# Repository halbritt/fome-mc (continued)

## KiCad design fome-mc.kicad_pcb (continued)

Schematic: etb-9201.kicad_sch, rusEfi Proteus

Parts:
C201, C202: 10n; C_0603_1608Metric; LCSC C344025
C1201: 2.2u; C_1206_3216Metric; LCSC C90787
R210: 10k; R_0402_1005Metric; LCSC C25744
U201: TLE9201SG; Infineon_PG-DSO-12-9; LCSC C2653438

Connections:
+3V3: R210.2, U201.2 (VSO); also elsewhere on the board
/12V_MR: C1201.2, U201.4 (VS); also elsewhere on the board
/ETB1_DIR: U201.1 (DIR); also elsewhere on the board
/ETB1_DIS: R210.1, U201.11 (DIS); also elsewhere on the board
/ETB1_OUT+: C201.2, U201.5 (OUT1); also elsewhere on the board
/ETB1_OUT-: C202.1, U201.7 (OUT2); also elsewhere on the board
/ETB1_PWM: U201.12 (PWM); also elsewhere on the board

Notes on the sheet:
IFX9201 also acceptable

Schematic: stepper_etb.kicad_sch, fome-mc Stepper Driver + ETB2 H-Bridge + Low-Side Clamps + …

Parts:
C203: 10n; C_0603_1608Metric; LCSC C344025
C204, C205: 100n; C_0603_1608Metric; LCSC C161115
C206: 470n; C_0603_1608Metric; LCSC C1623
D201, D202, D203, D204: B340A-13-F; D_SMA; LCSC C85098; not fitted
D205, D206, D207, D208, D209: B340A-13-F; D_SMA; LCSC C85098
D210: BZT52C6V8; D_SOD-123; LCSC C173404
D211: B5819W; D_SOD-123; LCSC C8598
R209, R218: 12k; R_0402_1005Metric; LCSC C25752
R211: 1M; R_0603_1608Metric; LCSC C22935
R212: 2.2k; R_0603_1608Metric; LCSC C4190
R213, R214: 200m; R_1206_3216Metric; LCSC C25335
R215: 33k; R_0402_1005Metric; LCSC C25779
R216, R217: 10k; R_0402_1005Metric; LCSC C25744
U202: DRV8825PWPR; HTSSOP-28-1EP_4.4x9.7mm_P0.65mm_EP2.85x5.4mm; LCSC C81582
U203: TLE9201SG; Infineon_PG-DSO-12-9; LCSC C2653438

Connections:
+3V3: D211.1 (K), R215.1, U202.16 (nRESET), U202.17 (nSLEEP), U203.2 (VSO); also elsewhere on the board
/12V_MR: C204.2, C205.1, D201.1 (K), D202.1 (K), D203.1 (K), D204.1 (K), D205.1 (K), D206.1 (K), D207.1 (K), D208.1 (K), D209.1 (K), R211.2, R212.1, U202.4 (VMA), U202.11 (VMB), U203.4 (VS); also elsewhere on the board
/BOOT0_NET: R209.2; also elsewhere on the board
/ETB2_DIR: U203.1 (DIR); also elsewhere on the board
/ETB2_DIS: U203.11 (DIS); also elsewhere on the board
/ETB2_OUT+: U203.5 (OUT1); also elsewhere on the board
/ETB2_OUT-: U203.7 (OUT2); also elsewhere on the board
/ETB2_PWM: U203.12 (PWM); also elsewhere on the board
/LS1: D201.2 (A); also elsewhere on the board
/LS2: D202.2 (A); also elsewhere on the board
/LS3: D203.2 (A); also elsewhere on the board
/LS4: D204.2 (A); also elsewhere on the board
/LS5: D205.2 (A); also elsewhere on the board
/LS6: D206.2 (A); also elsewhere on the board
/LS7: D207.2 (A); also elsewhere on the board
/LS8: D208.2 (A), R212.2; also elsewhere on the board
/LS9: U202.22 (STEP); also elsewhere on the board
/LS12: U202.20 (DIR); also elsewhere on the board
/MAIN_RLY: D209.2 (A); also elsewhere on the board
/PB8_STEP_EN: U202.21 (nENBL); also elsewhere on the board
/RC2: D211.2 (A), R217.2, R218.1; also elsewhere on the board
/STEP_1A: U202.5 (AOUT1); also elsewhere on the board
/STEP_1B: U202.7 (AOUT2); also elsewhere on the board
/STEP_2A: U202.10 (BOUT1); also elsewhere on the board
/STEP_2B: U202.8 (BOUT2); also elsewhere on the board
/USB_VBUS_BOOT0: D210.1 (K), R217.1; also elsewhere on the board
unnamed: D210.2 (A), R209.1
unnamed: R215.2, R216.1, U202.12 (AVREF), U202.13 (BVREF)
unnamed: C203.1, U202.1 (CP1)
unnamed: C203.2, U202.2 (CP2)
unnamed: R213.1, U202.6 (ISENA)
unnamed: R214.1, U202.9 (ISENB)
unnamed: C206.1, U202.15 (V3P3OUT)
unnamed: C204.1, R211.1, U202.3 (VCP)

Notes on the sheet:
D201..D204: DNP on INJ1..4 (/LS1../LS4) so U1001/U1002 VNLD5090TR-E use internal 42V active clamp for fast injector turn-off. D205..D209: Populated on LS5..LS8 & MAIN_RLY inductive relay/solenoid channels.

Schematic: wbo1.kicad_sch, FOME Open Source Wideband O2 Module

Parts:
C301, C304, C306, C307, C317: 1u; C_0402_1005Metric; LCSC C52923
C302, C305, C308, C309, C311, C312, C313, C314, C316: 100n; C_0402_1005Metric; LCSC C1525
C303: 33n; C_0402_1005Metric; LCSC C415530
C310: 4.7u; C_0603_1608Metric; LCSC C19666
D301, D304: RED; LED_0603_1608Metric; LCSC C2286
D302: GREEN; LED_0603_1608Metric; LCSC C12624
D303: BLUE; LED_0603_1608Metric; LCSC C2288
Q301: VND14NV04; TO-252-2; LCSC C2649436
R301, R302, R313, R318, R325, R326, R327, R330: 1k; R_0402_1005Metric; LCSC C11702
R303, R304, R311, R312, R321, R329, R333, R334: 10k; R_0402_1005Metric; LCSC C25744
R305, R307: 27k; R_0402_1005Metric; LCSC C25771
R306: 22k; R_0402_1005Metric; LCSC C25768
R308: 47; R_0402_1005Metric; LCSC C25118
R309: 10; R_0402_1005Metric; LCSC C25077
R310: 61.9; R_0603_1608Metric; LCSC C2087389
R314: 62k; R_0603_1608Metric; LCSC C23221
R315, R317, R320: 100k; R_0402_1005Metric; LCSC C25741
R316: 6.8k; R_0402_1005Metric; LCSC C25917
R319: 47k; R_0402_1005Metric; LCSC C25792
R324: 3.3k; R_0402_1005Metric; LCSC C25890
R331, R332: 68k; R_0402_1005Metric; LCSC C36871
U301: MCP6004; TSSOP-14_4.4x5mm_P0.65mm; LCSC C50282
U302: STM32F042K6Tx; LQFP-32_7x7mm_P0.8mm; LCSC C69216
U303: REF3033; SOT-23; LCSC C36658
U305: AD8628; TSOT-23-5; LCSC C29309
U307: TJA1051T-3; SOIC-8_3.9x4.9mm_P1.27mm; LCSC C38695
U309: XC6206P332MR; SOT-23; LCSC C5446

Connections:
+3V3_WBO1: C305.1, C310.1, C312.1, C313.1, C314.1, R314.1, R318.2, U301.4 (V+), U302.1 (VDD), U302.17 (VDDIO2), U305.5 (V+), U307.5 (VIO), U309.2 (VO)
+5V: C308.1, C317.1, U303.1 (IN), U307.3 (VCC), U309.3 (VI); also elsewhere on the board
/12V_MR: R320.1; also elsewhere on the board
/CAN2+: U307.7 (CANH); also elsewhere on the board
/CAN2-: U307.6 (CANL); also elsewhere on the board
/WBO1_BOOT0: R329.2, U302.31 (PB8); also elsewhere on the board
/WBO1_H-: Q301.2 (D); also elsewhere on the board
/WBO1_IP: R310.2, R312.2; also elsewhere on the board
/WBO1_NRST: C316.1, U302.4 (NRST); also elsewhere on the board
/WBO1_RTRIM: R308.1, R310.1, R311.2, R334.1; also elsewhere on the board
/WBO1_UN: C302.1, R314.2, U301.10 (+); also elsewhere on the board
/WBO1_VM: C304.1, R303.1, R309.1, U302.7 (PA1); also elsewhere on the board
/wbo1/CAN_RX: U302.21 (PA11), U307.4 (RXD)
/wbo1/CAN_TX: U302.22 (PA12), U307.1 (TXD)
/wbo1/Ip_dac: R331.1, U302.12 (PA6)
/wbo1/Ip_sense: C311.1, R324.2, U302.8 (PA2)
/wbo1/LED_BLUE: D303.2 (A), U302.28 (PB5)
/wbo1/LED_GREEN: D302.2 (A), U302.29 (PB6)
/wbo1/LSU_Un_sense: R304.1, U301.8, U301.9 (-)
/wbo1/Nernst_esr_drive_42: R316.2, U302.26 (PB3)
/wbo1/Nernst_esr_drive_49: R306.2, U302.30 (PB7)
/wbo1/Nernst_esr_drive_adv: R319.2, U302.27 (PB4)
/wbo1/Un_sense: R307.2, U301.7, U302.6 (PA0)
/wbo1/Vm: R309.2, R315.2, R332.2, U301.13 (-), U301.14, U302.9 (PA3)
/wbo1/heater_pwm: R325.2, R326.2, R327.2, U302.13 (PA7)
unnamed: C302.2, R306.1, R316.1, R319.1
unnamed: C303.1, R308.2, R333.1, U301.1
unnamed: D301.2 (A), R327.1
unnamed: D302.1 (K), R330.2
unnamed: D303.1 (K), R313.2
unnamed: D304.2 (A), R318.1
unnamed: Q301.1 (G), R325.1
unnamed: R317.1, R324.1, U305.1
unnamed: R332.1, R334.2, U301.3 (+)
unnamed: C303.2, R331.2, R333.2, U301.2 (-)
unnamed: R304.2, R305.1, U301.5 (+)
unnamed: R303.2, R307.1, U301.6 (-)
unnamed: C301.1, R301.2, R302.1, U301.12 (+)
unnamed: C306.1, R320.2, R321.1, U302.14 (PB0)
unnamed: R312.1, R315.1, U305.3 (+)
unnamed: R311.1, R317.2, U305.4 (-)
VDDA_WBO1: C307.1, C309.1, R301.1, U302.5 (VDDA), U303.2 (OUT)

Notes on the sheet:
Un_sense = 2.7 * (Un - Vm)
Nernst Internal Resistance Measurement
Pump Driver
Nernst Sense Voltage Buffer
PF0/1 grounded on Hellen module, do not connect
Nernst Bias Current
Ip_sense = 10 * (LSU_Ip - LSU_Rtrim)
Virtual Ground Generation
Nernst Sense
Pump Current Sense
SEL_1, SEL_2: low, low = idx 2 low, float = idx 0 low, high = idx 3 float, low = idx 4 float, float = read index from flash cfg float, high = idx 1 high, low = idx 5 high, float = idx 6 high, high = idx 7

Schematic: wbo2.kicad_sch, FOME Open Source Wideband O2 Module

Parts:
C401, C404, C406, C407, C417: 1u; C_0402_1005Metric; LCSC C52923
C402, C405, C408, C409, C411, C412, C413, C414, C416: 100n; C_0402_1005Metric; LCSC C1525
C403: 33n; C_0402_1005Metric; LCSC C415530
C410: 4.7u; C_0603_1608Metric; LCSC C19666
D401, D404: RED; LED_0603_1608Metric; LCSC C2286
D402: GREEN; LED_0603_1608Metric; LCSC C12624
D403: BLUE; LED_0603_1608Metric; LCSC C2288
Q401: VND14NV04; TO-252-2; LCSC C2649436
R401, R402, R413, R418, R425, R426, R427, R430: 1k; R_0402_1005Metric; LCSC C11702
R403, R404, R411, R412, R421, R429, R433, R434: 10k; R_0402_1005Metric; LCSC C25744
R405, R407: 27k; R_0402_1005Metric; LCSC C25771
R406: 22k; R_0402_1005Metric; LCSC C25768
R408: 47; R_0402_1005Metric; LCSC C25118
R409: 10; R_0402_1005Metric; LCSC C25077
R410: 61.9; R_0603_1608Metric; LCSC C2087389
R414: 62k; R_0603_1608Metric; LCSC C23221
R415, R417, R420: 100k; R_0402_1005Metric; LCSC C25741
R416: 6.8k; R_0402_1005Metric; LCSC C25917
R419: 47k; R_0402_1005Metric; LCSC C25792
R424: 3.3k; R_0402_1005Metric; LCSC C25890
R431, R432: 68k; R_0402_1005Metric; LCSC C36871
U401: MCP6004; TSSOP-14_4.4x5mm_P0.65mm; LCSC C50282
U402: STM32F042K6Tx; LQFP-32_7x7mm_P0.8mm; LCSC C69216
U403: REF3033; SOT-23; LCSC C36658
U405: AD8628; TSOT-23-5; LCSC C29309
U407: TJA1051T-3; SOIC-8_3.9x4.9mm_P1.27mm; LCSC C38695
U409: XC6206P332MR; SOT-23; LCSC C5446

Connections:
+3V3_WBO2: C405.1, C410.1, C412.1, C413.1, C414.1, R414.1, R418.2, U401.4 (V+), U402.1 (VDD), U402.17 (VDDIO2), U402.18 (PA8), U405.5 (V+), U407.5 (VIO), U409.2 (VO)
+5V: C408.1, C417.1, U403.1 (IN), U407.3 (VCC), U409.3 (VI); also elsewhere on the board
/12V_MR: R420.1; also elsewhere on the board
/CAN2+: U407.7 (CANH); also elsewhere on the board
/CAN2-: U407.6 (CANL); also elsewhere on the board
/WBO2_BOOT0: R429.2, U402.31 (PB8); also elsewhere on the board
/WBO2_H-: Q401.2 (D); also elsewhere on the board
/WBO2_IP: R410.2, R412.2; also elsewhere on the board
/WBO2_NRST: C416.1, U402.4 (NRST); also elsewhere on the board
/WBO2_RTRIM: R408.1, R410.1, R411.2, R434.1; also elsewhere on the board
/WBO2_UN: C402.1, R414.2, U401.10 (+); also elsewhere on the board
/WBO2_VM: C404.1, R403.1, R409.1, U402.7 (PA1); also elsewhere on the board
/wbo2/CAN_RX: U402.21 (PA11), U407.4 (RXD)
/wbo2/CAN_TX: U402.22 (PA12), U407.1 (TXD)
/wbo2/Ip_dac: R431.1, U402.12 (PA6)
/wbo2/Ip_sense: C411.1, R424.2, U402.8 (PA2)
/wbo2/LED_BLUE: D403.2 (A), U402.28 (PB5)
/wbo2/LED_GREEN: D402.2 (A), U402.29 (PB6)
/wbo2/LSU_Un_sense: R404.1, U401.8, U401.9 (-)
/wbo2/Nernst_esr_drive_42: R416.2, U402.26 (PB3)
/wbo2/Nernst_esr_drive_49: R406.2, U402.30 (PB7)
/wbo2/Nernst_esr_drive_adv: R419.2, U402.27 (PB4)
/wbo2/Un_sense: R407.2, U401.7, U402.6 (PA0)
/wbo2/Vm: R409.2, R415.2, R432.2, U401.13 (-), U401.14, U402.9 (PA3)
/wbo2/heater_pwm: R425.2, R426.2, R427.2, U402.13 (PA7)
unnamed: C402.2, R406.1, R416.1, R419.1
unnamed: C403.1, R408.2, R433.1, U401.1
unnamed: D401.2 (A), R427.1
unnamed: D402.1 (K), R430.2
unnamed: D403.1 (K), R413.2
unnamed: D404.2 (A), R418.1
unnamed: Q401.1 (G), R425.1
unnamed: R417.1, R424.1, U405.1
unnamed: R432.1, R434.2, U401.3 (+)
unnamed: C403.2, R431.2, R433.2, U401.2 (-)
unnamed: R404.2, R405.1, U401.5 (+)
unnamed: R403.2, R407.1, U401.6 (-)
unnamed: C401.1, R401.2, R402.1, U401.12 (+)
unnamed: C406.1, R420.2, R421.1, U402.14 (PB0)
unnamed: R412.1, R415.1, U405.3 (+)
unnamed: R411.1, R417.2, U405.4 (-)
VDDA_WBO2: C407.1, C409.1, R401.1, U402.5 (VDDA), U403.2 (OUT)

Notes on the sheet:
Un_sense = 2.7 * (Un - Vm)
Nernst Internal Resistance Measurement
Pump Driver
Nernst Sense Voltage Buffer
PF0/1 grounded on Hellen module, do not connect
Nernst Bias Current
Ip_sense = 10 * (LSU_Ip - LSU_Rtrim)
Virtual Ground Generation
Nernst Sense
Pump Current Sense
SEL_1, SEL_2: low, low = idx 2 low, float = idx 0 low, high = idx 3 float, low = idx 4 float, float = read index from flash cfg float, high = idx 1 high, low = idx 5 high, float = idx 6 high, high = idx 7

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
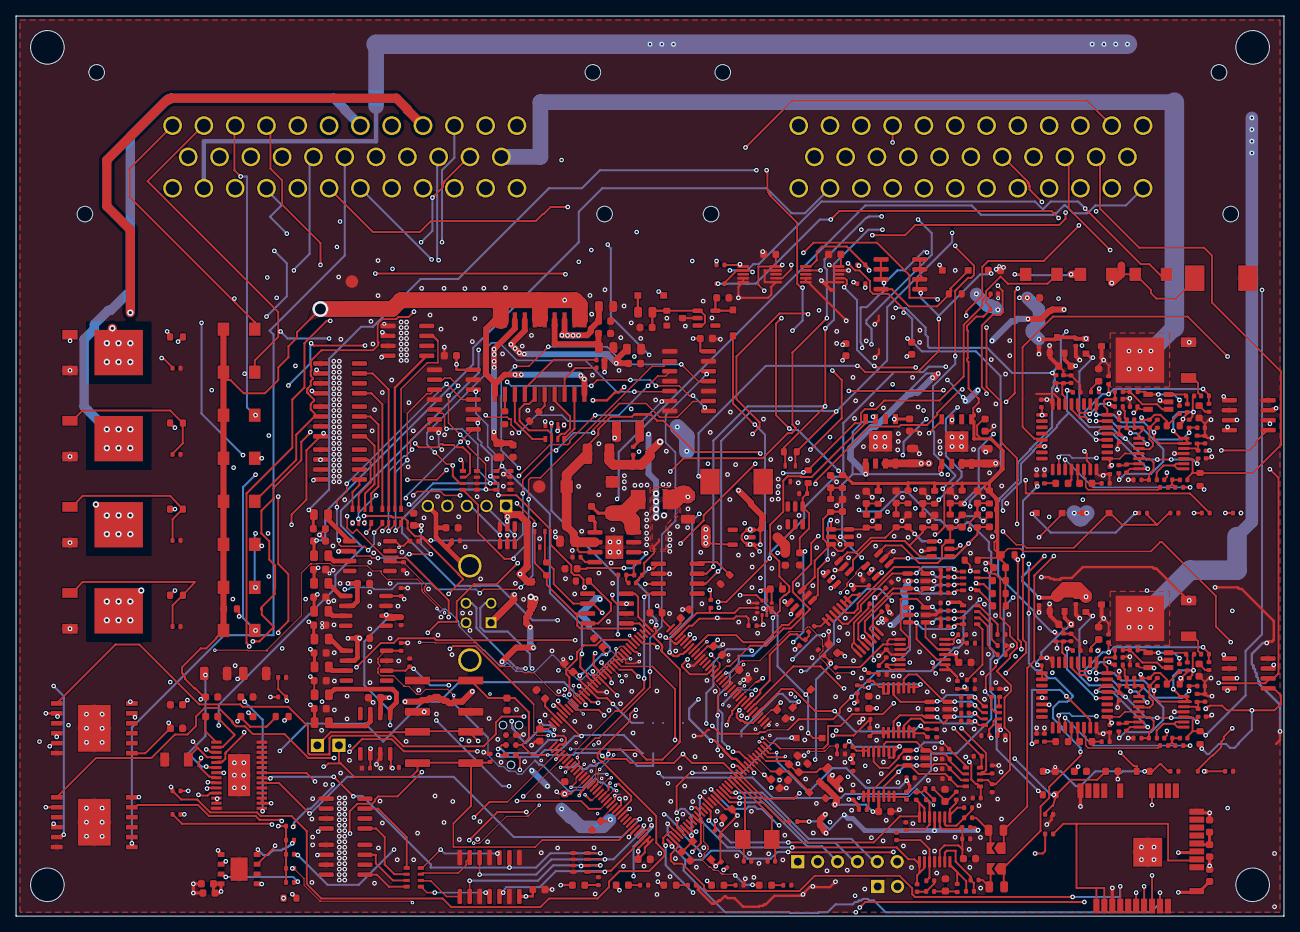
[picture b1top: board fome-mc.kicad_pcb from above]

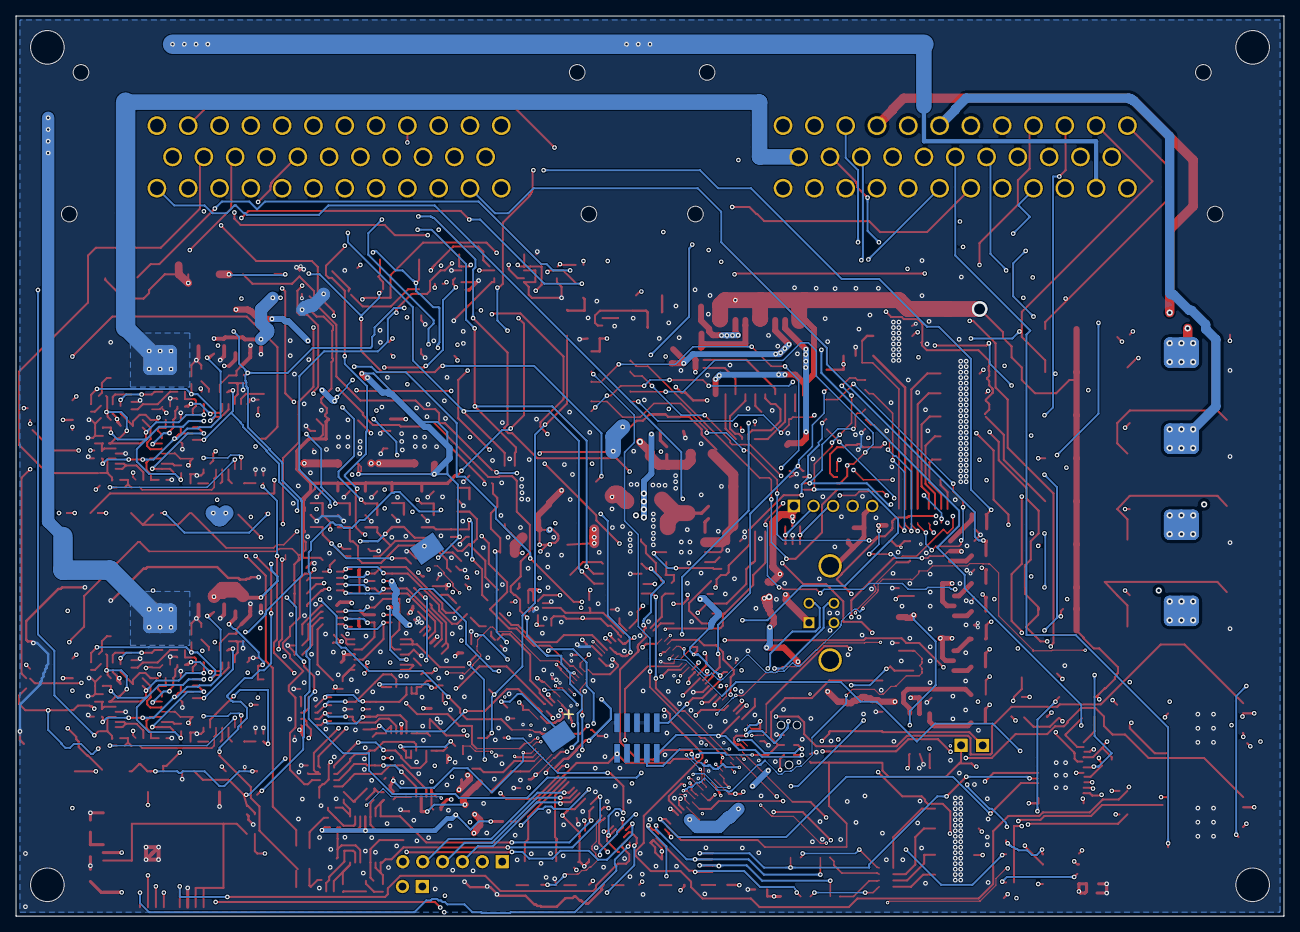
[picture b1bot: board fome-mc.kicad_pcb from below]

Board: 4 copper layers, 162.0 x 115.0 mm, 514 parts (2 on the bottom side), 389 nets.

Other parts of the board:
H1, H2, H3, H4: MountingHole; MountingHole_4.3mm_M4

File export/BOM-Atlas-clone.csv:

Comment,Designator,Footprint,LCSC
Ferrite_Bead,FB1,L_0805_2012Metric,C1015
SN74LVC2G17DB,"U10,U14,U8,U9",SOT-23-6,C10429
USBLC6-2SC6,U27,SOT-23-6,C111212
8MHz,Y1,Crystal_SMD_5032-2Pin_5.0x3.2mm,C115962
1k,"R1501,R1502,R1503,R1504,R1601,R1602,R1603,R1604,R87,R88",R_0402_1005Metric,C11702
REF3333,U23,SOT-23,C130016
2.7k,"R23,R24,R25,R26,R27,R28,R29,R30,R31,R32,R33,R34,R35,R36,R37,R38,R39,R40,R41,R42",R_0603_1608Metric,C13167
330p,"C11,C20,C21",C_0402_1005Metric,C13533
10u,"C12,C13",C_1206_3216Metric,C13585
100n,"C10,C40,C41,C46,C51,C56,C61,C62,C63,C64,C67,C68,C69,C70,C71,C73,C79,C81,C83,C89,C91,C92,C97,C98,C103,C104,C105,C106",C_0603_1608Metric,C14663
SM15T33CA,D1,D_SMC,C151281
100n,"C42,C43,C44,C45,C47,C48,C49,C50,C52,C53,C54,C55,C57,C58,C59,C60",C_0402_1005Metric,C1525
PESD1CAN-UX,"D4,D5",SOT-323_SC-70,C907839
33p,"C74,C75",C_0402_1005Metric,C1562
47p,"C22,C23",C_0402_1005Metric,C1567
1u,"C2,C3,C5,C7,C84,C9",C_0603_1608Metric,C15849
1n,"C24,C25,C26,C27,C28,C29,C30,C31,C32,C33,C34,C35,C36,C37,C38,C39",C_0603_1608Metric,C1588
680p,"C18,C19",C_0603_1608Metric,C1630
Micro_SD_Card,J10,microSD_HC_Wuerth_693072010801,C164170
MIC4427,"U42,U43,U44,U45",SO-8_3.9x4.9mm_P1.27mm,C171845
100,"R108,R109,R110,R111,R112,R113,R114,R115",R_0805_2012Metric,C17408
4.7k,"R103,R104,R105,R106,R107",R_0805_2012Metric,C17673
LMR14020,U3,SOIC-8-1EP_3.9x4.9mm_P1.27mm_EP2.29x3mm,C187824
4.7u,"C14,C4,C65,C66,C72,C76,C80,C82,C107",C_0603_1608Metric,C19666
1k,"RN10,RN5,RN6,RN7,RN8,RN9",R_Array_Convex_4x0603,C20197
Polyfuse,"F1,F2",R_1206_3216Metric,C207035
VNLD5090,"U1001,U1002,U1101,U1102,U1201,U1202",SOIC-8_3.9x4.9mm_P1.27mm,C222209
120,"R10,R101,R102,R7,R8,R9",R_0603_1608Metric,C22787
RED,D10,LED_0603_1608Metric_Castellated,C2286
82k,"R96,R116,R120",R_0603_1608Metric,C23254
2.2u,"C77,C78,C90",C_0603_1608Metric,C23630
1,R2,R_0402_1005Metric,C25086
330,"R91,R92,R93,R94,R95",R_0402_1005Metric,C25104
100k,"R13,R14,R19,R20,R98",R_0402_1005Metric,C25741
10k,"R1,R100,R3,R4,R47,R48,R49,R50,R59,R60,R61,R62,R71,R72,R73,R74,R83,R84,R85,R86,R89,R90,R97,R99,R117,R118,R119,R121,R123",R_0402_1005Metric,C25744
12k,"R17,R18,R5",R_0402_1005Metric,C25752
33k,"R11,R12,R21,R22",R_0402_1005Metric,C25779
470k,"R15,R16,R51,R52,R53,R54,R63,R64,R65,R66,R75,R76,R77,R78",R_0402_1005Metric,C25790
5.6k,"R43,R44,R45,R46,R55,R56,R57,R58,R67,R68,R69,R70,R79,R80,R81,R82",R_0402_1005Metric,C25908
10k,"RN1,RN11,RN2,RN3,RN4",R_Array_Convex_4x0603,C29718
SW_Push,"SW1,SW2",SW_SPST_EVQQ2,C318887
PSM712-LF-T7,IC1,SOT-23,C32677
68k,"R6,R122",R_0402_1005Metric,C36871
TLS115D0E,"U1,U2",Infineon_PG-DSO-8-43,C3747428
10u,"L2,L3",MWSA0503,C408412
MCP6004,"U15,U17,U19,U21,U7",TSSOP-14_4.4x5mm_P0.65mm,C50282
3.3n,"C16,C17",C_0805_2012Metric,C472819
MIC5205-3.3YM5,U41,SOT-23-5,C5370979
10n,"C100,C101,C102,C15,C8,C85,C86,C87,C88,C93,C94,C95,C96,C99",C_0603_1608Metric,C57112
AMS1117-3.3,U6,SOT-223-3_TabPin2,C6186
ORANGE,D13,LED_0603_1608Metric_Castellated,C2287
BLUE,D11,LED_0603_1608Metric_Castellated,C2288
GREEN,"D12,D9",LED_0603_1608Metric_Castellated,C12624
MCP2551-I-SN,"U4,U5",SOIC-8_3.9x4.9mm_P1.27mm,C7376
2.2u,L1,L_1210_3225Metric,C75646
BTS716G,U40,Infineon_PG-DSO-20-32,C85135
SRV05-4,"D15,U11,U12,U13,U16,U18,U20,U22",SOT-23-6,C85364
schottky,"D14,D16,D17,D6,D7,D8",D_SOD-123,C8598
D_Schottky,"D2,D3,D18",D_SMA,C8678
STM32H753ZIT6,U26,LQFP-144_20x20mm_P0.5mm,C730207
LPS25HBTR,U24,ST_HLGA-10_2.5x2.5mm_P0.6mm_LayoutBorder3x2y,C87898
47u_50V_Hybrid,"C1,C6",CP_Elec_8x10.5,C454346
S3225SMD32.768KOSC,U28,SMD3225-4P,C7431189
LM2733XMFX/NOPB,U46,SOT-23-5,C80169
